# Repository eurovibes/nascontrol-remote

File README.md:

<!-- SPDX-FileCopyrightText: 2023 Benedikt Spranger <b.spranger@linutronix.de> -->
<!-- SPDX-License-Identifier: CERN-OHL-S-2.0 -->

# NAScontrol - A NAS control board / remote side

## License rules

nascontrol-remote is provided under the terms of the CERN-OHL-S license
version 2 as provided in the LICENSES/CERN-OHL-S-2.0 file.

Instead of adding license boilerplates to the individual files,
nascontrol-remote uses SPDX license identifiers, which are machine parseable
and considered legaly equivalent.

The SPDX license identifier in nascontrol-remote shall be added at the first
possible line in a file which can contain a comment. This is normally the
first line except for scripts. Scripts require the #!PATH_TO_INTERPRETER tag
in the first line; place the SPDX identifier into the second line.

The SPDX license identifier is added in form of a comment.

## Copyright and License

> Copyright Benedikt Spranger 2023.
> This source describes Open Hardware and is licensed under the CERNOHL-S v2.
> You may redistribute and modify this source and make products using it
> under the terms of the CERN-OHL-S v2 (https://ohwr.org/cern ohl s v2.txt ).
> This source is distributed WITHOUT ANY EXPRESS OR IMPLIED WARRANTY, INCLUDING
> OF MERCHANTABILITY, SATISFACTORY QUALITY AND FITNESS FOR A PARTICULAR PURPOSE.
> Please see the CERN-OHL-S v2 for applicable conditions.
> Source location: https://github.com/eurovibes/nascontrol-remote
> As per CERN-OHL-S v2 section 4, should You produce hardware based
> on this source, You must where practicable maintain the Source Location
> visible on the external case of the nascontrol-remote or other products you
> make using this source.

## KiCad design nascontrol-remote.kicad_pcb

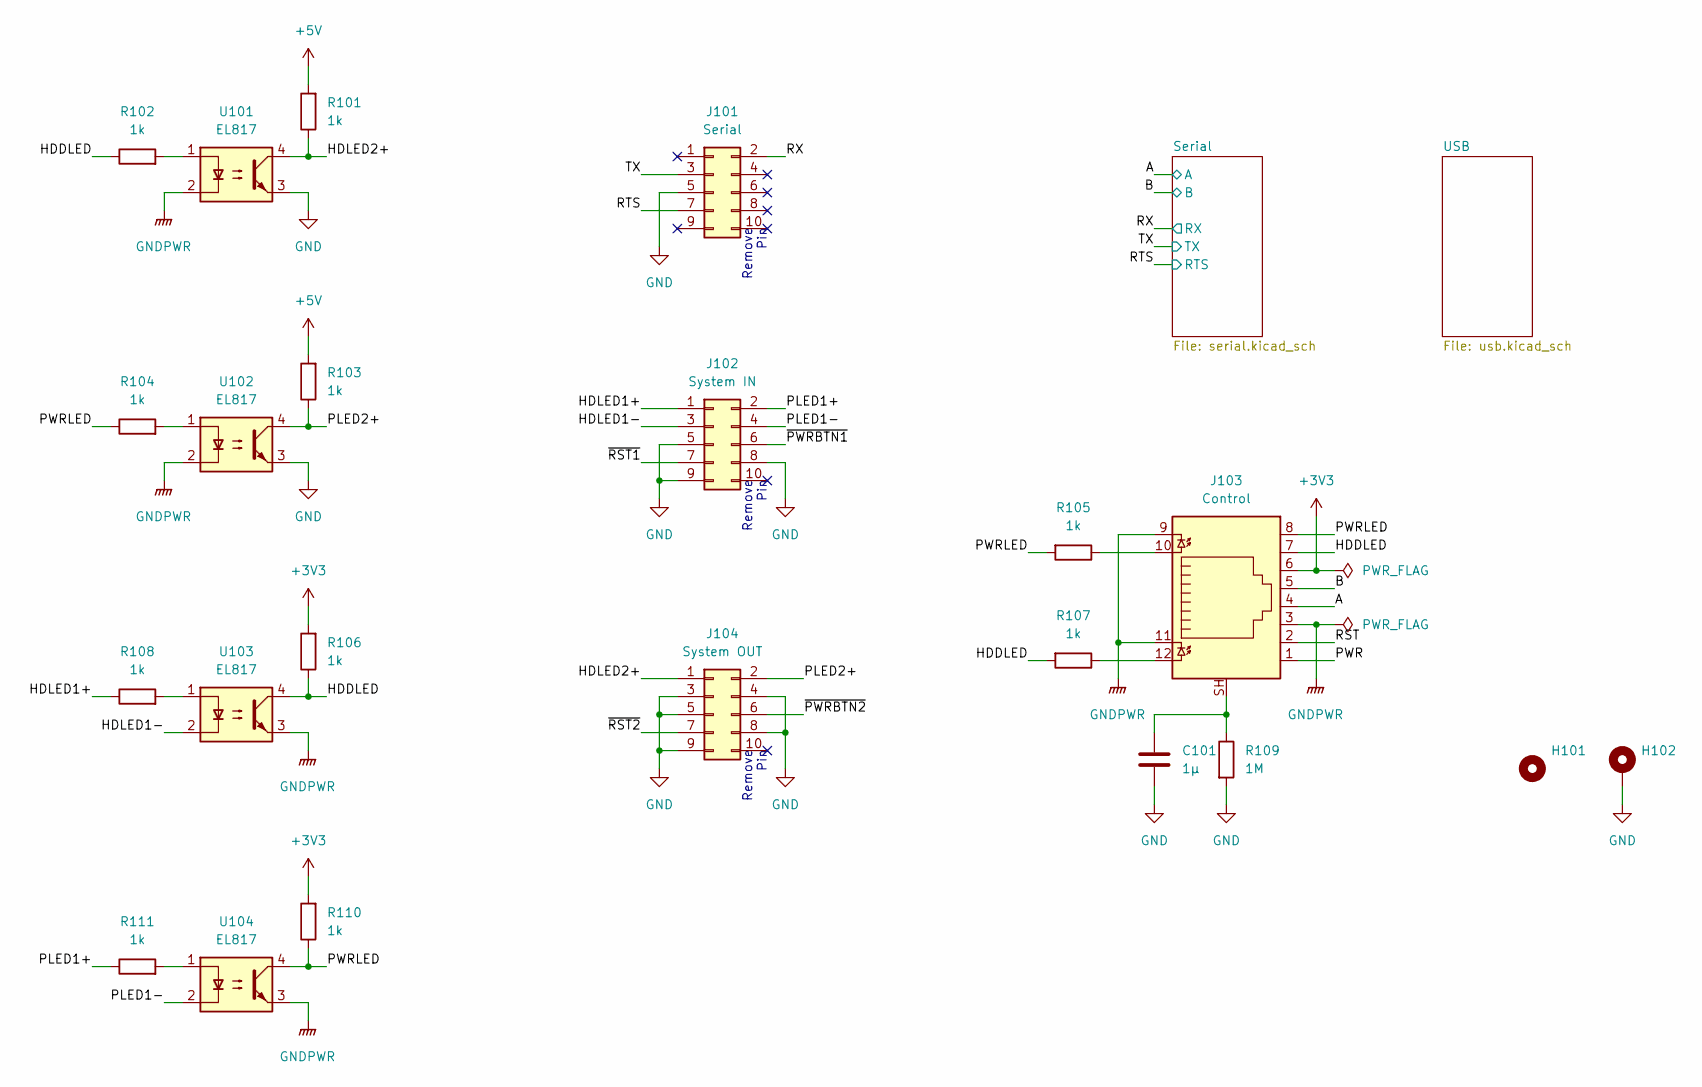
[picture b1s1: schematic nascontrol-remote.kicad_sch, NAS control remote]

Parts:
C101: 1µ; C_1206_3216Metric; mpn CL31B105KBHNNNE; LCSC# C1848
H101: MountingHole_3.2mm_M3; mpn N/A
H102: MountingHole_3.2mm_M3_Pad; mpn N/A
J101: Serial; PinHeader_2x05_P2.54mm_Vertical; mpn DS1021-2*5SF11-B
J102: System IN; PinHeader_2x05_P2.54mm_Vertical; mpn DS1021-2*5SF11-B
J103: Control; RJ45_Amphenol_RJHSE538X; mpn RJHSE-538B
J104: System OUT; PinHeader_2x05_P2.54mm_Vertical; mpn DS1021-2*5SF11-B
R101, R102, R103, R104, R105, R106, R107, R108, R110, R111: 1k; R_0402_1005Metric; mpn 0402WGF1001TCE; LCSC# C11702
R109: 1M; R_0805_2012Metric; mpn 0805W8F1004T5E; LCSC# C17514
U101, U102, U103, U104: EL817; SMDIP-4_W7.62mm; mpn EL817S1(C)(TU)-F; LCSC# C106900

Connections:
+3V3: J103.6, R106.2, R110.2; also elsewhere on the board
+5V: R101.2, R103.2; also elsewhere on the board
/A: J103.4; also elsewhere on the board
/B: J103.5; also elsewhere on the board
/HDDLED: J103.7, R102.1, R106.1, R107.2, U103.4
/HDLED1+: J102.1, R108.1
/HDLED1-: J102.3, U103.2
/HDLED2+: J104.1, R101.1, U101.4
/PLED1+: J102.2, R111.1
/PLED1-: J102.4, U104.2
/PLED2+: J104.2, R103.1, U102.4
/PWR: J103.1
/PWRLED: J103.8, R104.1, R105.2, R110.1, U104.4
/RST: J103.2
/RTS: J101.7; also elsewhere on the board
/RX: J101.2; also elsewhere on the board
/TX: J101.3; also elsewhere on the board
/~PWRBTN1: J102.6
/~PWRBTN2: J104.6
/~RST1: J102.7
/~RST2: J104.7
GND: C101.2, H102.1, J101.5, J102.5, J102.8, J102.9, J104.3, J104.4, J104.5, J104.8, J104.9, R109.2, U101.3, U102.3; also elsewhere on the board
GNDPWR: J103.3, J103.9, J103.11, U101.2, U102.2, U103.3, U104.3; also elsewhere on the board
unnamed: C101.1, J103.SH, R109.1
unnamed: J103.10, R105.1
unnamed: J103.12, R107.1
unnamed: R102.2, U101.1
unnamed: R104.2, U102.1
unnamed: R108.2, U103.1
unnamed: R111.2, U104.1

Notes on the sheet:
Remove Pin

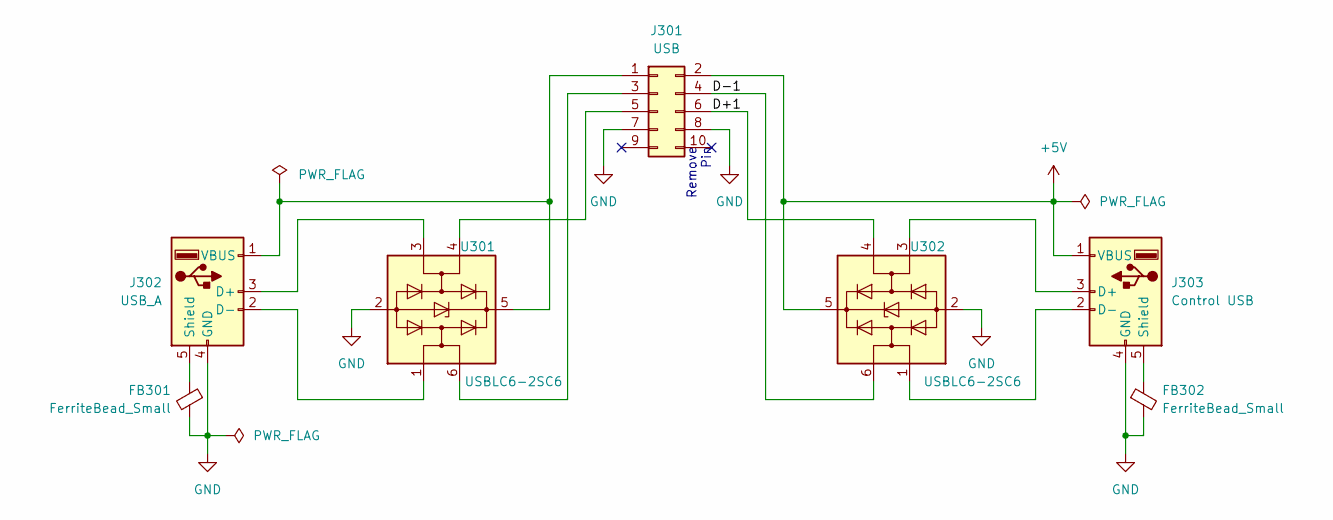
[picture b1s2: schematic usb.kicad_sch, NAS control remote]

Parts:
FB301, FB302: FerriteBead_Small; L_0805_2012Metric; mpn GZ2012D101TF; LCSC# C1015
J301: USB; PinHeader_2x05_P2.54mm_Vertical; mpn DS1021-2*5SF11-B
J302: USB_A; USB_A_Molex_67643_Horizontal; mpn 676430910
J303: Control USB; USB_A_Molex_67643_Horizontal; mpn 676430910
U301, U302: USBLC6-2SC6; SOT-23-6; mpn USBLC6-2SC6; LCSC# C2827654

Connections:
+5V: J301.2, J303.1 (VBUS), U302.5 (VBUS); also elsewhere on the board
/USB/D+1: J301.6, U302.4 (I/O2)
/USB/D-1: J301.4, U302.6 (I/O1)
GND: FB301.2, FB302.2, J301.7, J301.8, J302.4 (GND), J303.4 (GND), U301.2 (GND), U302.2 (GND); also elsewhere on the board
unnamed: FB301.1, J302.5 (Shield)
unnamed: FB302.1, J303.5 (Shield)
unnamed: J301.1, J302.1 (VBUS), U301.5 (VBUS)
unnamed: J301.3, U301.6 (I/O1)
unnamed: J301.5, U301.4 (I/O2)
unnamed: J302.2 (D-), U301.1 (I/O1)
unnamed: J302.3 (D+), U301.3 (I/O2)
unnamed: J303.2 (D-), U302.1 (I/O1)
unnamed: J303.3 (D+), U302.3 (I/O2)

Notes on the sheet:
Remove Pin

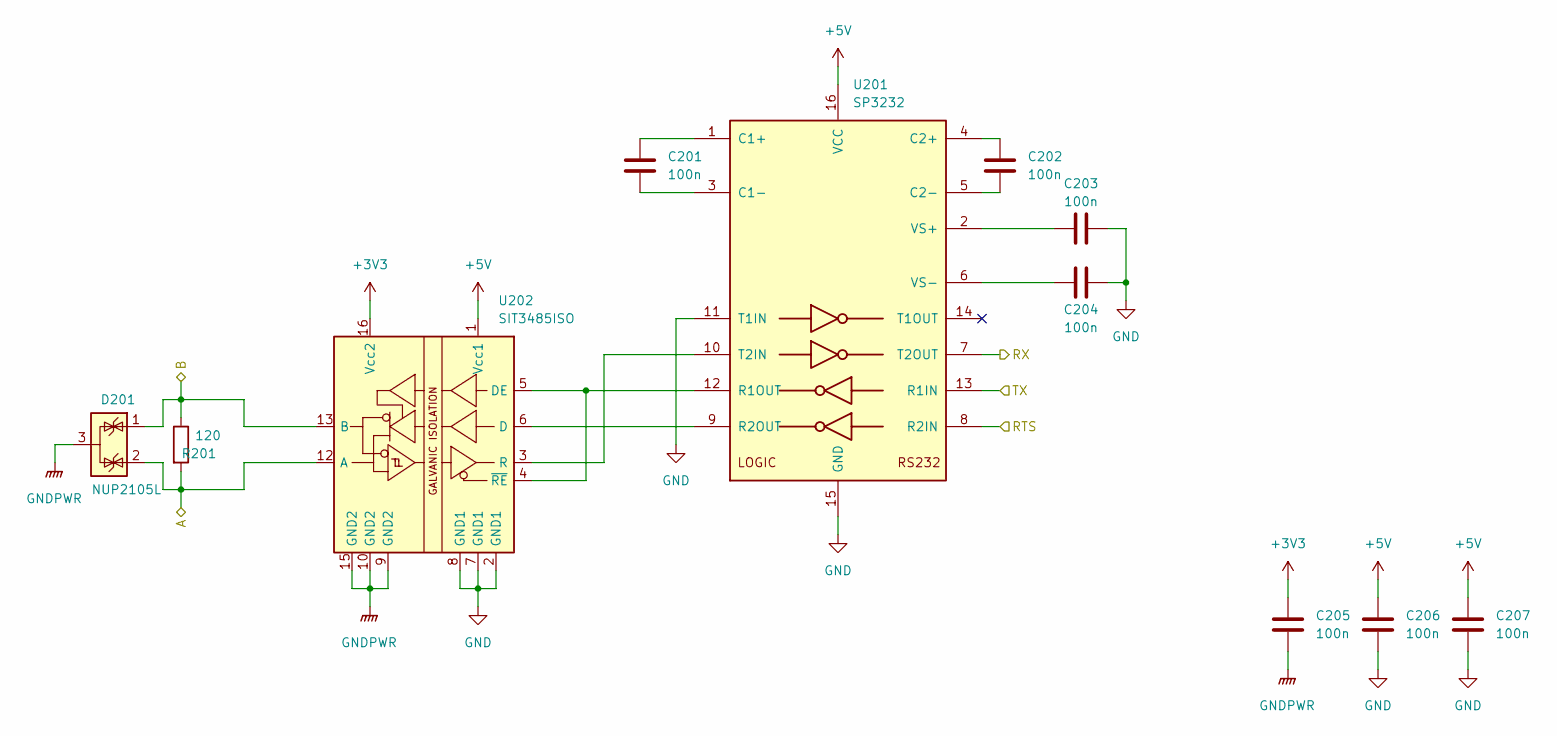
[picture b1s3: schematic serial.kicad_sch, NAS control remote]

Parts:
C201, C202, C203, C204, C205, C206, C207: 100n; C_0402_1005Metric; mpn CL05B104KB54PNC; LCSC# C307331
D201: NUP2105L; SOT-23; mpn NUP2105LT1G; LCSC# C2890118
R201: 120; R_1206_3216Metric; mpn 1206W4F1200T5E; LCSC# C17909
U201: SP3232; TSSOP-16_4.4x5mm_P0.65mm; mpn SP3232EEY-L/TR; LCSC# C13482
U202: SIT3485ISO; SOIC-16W_7.5x10.3mm_P1.27mm; mpn SIT3485ISO; LCSC# C2974613

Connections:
+3V3: C205.1, U202.16 (Vcc2); also elsewhere on the board
+5V: C206.1, C207.1, U201.16 (VCC), U202.1 (Vcc1); also elsewhere on the board
/A: D201.2 (K), R201.2, U202.12 (A); also elsewhere on the board
/B: D201.1 (K), R201.1, U202.13 (B); also elsewhere on the board
/RTS: U201.8 (R2IN); also elsewhere on the board
/RX: U201.7 (T2OUT); also elsewhere on the board
/TX: U201.13 (R1IN); also elsewhere on the board
GND: C203.2, C204.2, C206.2, C207.2, U201.11 (T1IN), U201.15 (GND), U202.2 (GND1), U202.7 (GND1), U202.8 (GND1); also elsewhere on the board
GNDPWR: C205.2, D201.3 (A), U202.9 (GND2), U202.10 (GND2), U202.15 (GND2); also elsewhere on the board
unnamed: C201.1, U201.1 (C1+)
unnamed: C201.2, U201.3 (C1-)
unnamed: C202.1, U201.4 (C2+)
unnamed: C202.2, U201.5 (C2-)
unnamed: C203.1, U201.2 (VS+)
unnamed: C204.1, U201.6 (VS-)
unnamed: U201.9 (R2OUT), U202.6 (D)
unnamed: U201.10 (T2IN), U202.3 (R)
unnamed: U201.12 (R1OUT), U202.4 (~RE), U202.5 (DE)

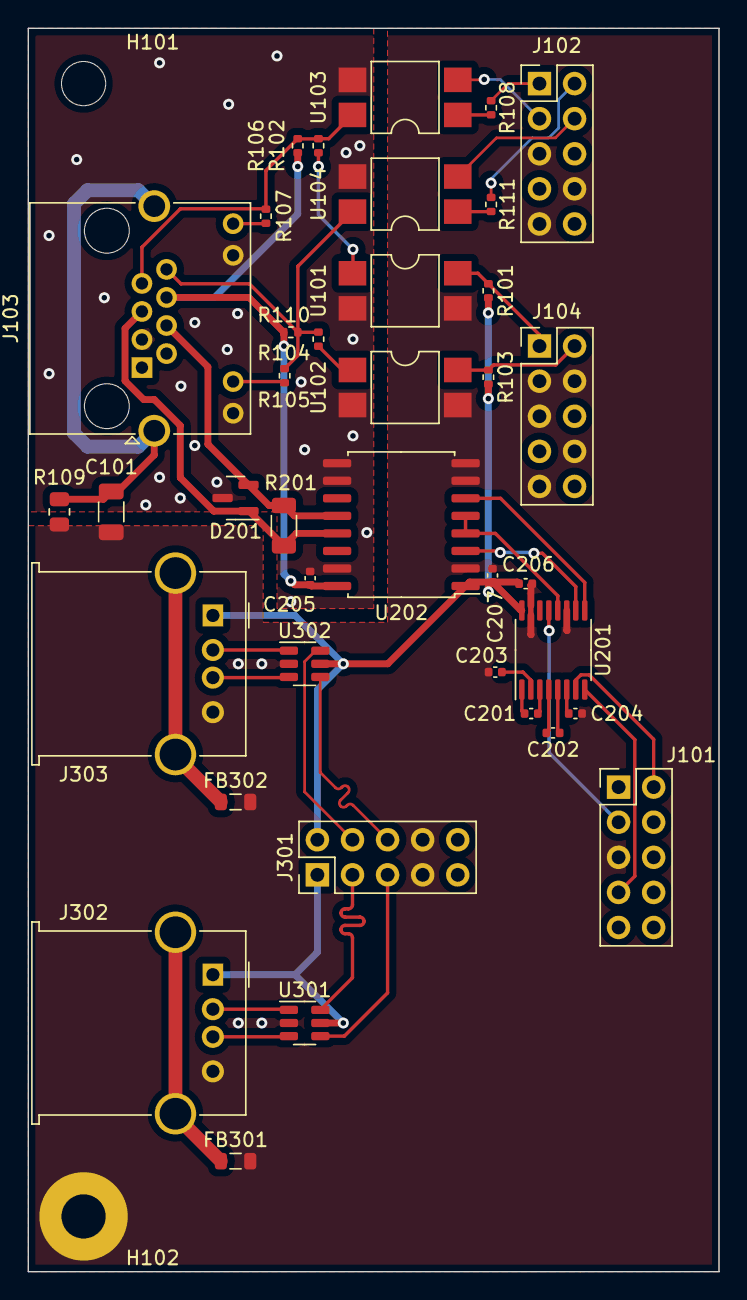
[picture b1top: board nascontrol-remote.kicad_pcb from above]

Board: 2 copper layers, 50.0 x 90.0 mm, 40 parts (0 on the bottom side), 44 nets.

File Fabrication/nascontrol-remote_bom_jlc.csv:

"Comment","Designator","Footprint","LCSC Part #"
"100n","C201,C202,C203,C204,C205,C206,C207","C_0402_1005Metric","C307331"
"1µ","C101","C_1206_3216Metric","C1848"
"NUP2105L","D201","SOT-23","C2890118"
"FerriteBead_Small","FB301,FB302","L_0805_2012Metric","C1015"
"120","R201","R_1206_3216Metric","C17909"
"1k","R101,R102,R103,R104,R105,R106,R107,R108,R110,R111","R_0402_1005Metric","C11702"
"1M","R109","R_0805_2012Metric","C17514"
"EL817","U101,U102,U103,U104","SMDIP-4_W7.62mm","C106900"
"SIT3485ISO","U202","SOIC-16W_7.5x10.3mm_P1.27mm","C2974613"
"SP3232","U201","TSSOP-16_4.4x5mm_P0.65mm","C13482"
"USBLC6-2SC6","U301,U302","SOT-23-6","C2827654"

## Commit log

2023-01-13 Initial gh-pages commit
2023-01-13 Deploying to gh-pages from @ eurovibes/nascontrol-remote@cebaea326f09a8d97db6b56e1a4afeae7c0cfc1c 🚀
2023-01-13 Initial
2023-01-13 Deploying to gh-pages from @ eurovibes/nascontrol-remote@80c99bc9eae50c1ce251ad5ec118a231412973b6 🚀
2023-01-20 Update node 12 actions
    Node 12 is EOL. Update Actions relaying on Node 12 to newer versions.
2023-01-20 Deploying to gh-pages from @ eurovibes/nascontrol-remote@dc477c232f6299f18bea7569463dc9692226e9f7 🚀
2023-01-21 Add missing 3D model
2023-01-21 WIP: Add enclosure
2023-01-21 Deploying to gh-pages from @ eurovibes/nascontrol-remote@b1e138f29dea12ac1ac24cc92560fedb23c52042 🚀
2024-01-20 Mark PCB
2024-01-20 Fix PWR and RST issue
2024-01-20 Inverse RJ45 connections
2024-01-20 Add Eurovibes logo
2024-01-20 Insulation cleanup
2024-01-20 Deploying to gh-pages from @ eurovibes/nascontrol-remote@de826c3027ba6282ef51d5a4c04e67440a6fd1b4 🚀
2024-01-20 Deploying to gh-pages from @ eurovibes/nascontrol-remote@f9d1beb82d66195b6cfbf28ac06cdd87eab78f55 🚀
2024-01-20 fix JLC BOM
2024-01-20 Deploying to gh-pages from @ eurovibes/nascontrol-remote@d6c1f96b70169e17c392b38f5232019822fb5f71 🚀

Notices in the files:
nascontrol-remote.kicad_sch:
This work is licensed under the CERN-OHL-S v2
